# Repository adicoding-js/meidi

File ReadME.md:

# MIDI Keypad

()

A custom USB MIDI controller built from scratch following Kai's MIDI Keypad tutorial. No stock firmware, no base project to extend, the tutorial hands you a KiCad library and component options and says figure out your own layout, so this is my own hardware config and (once I get to it) my own firmware mapping it to MIDI.

## What it is

7 capacitive touch keys mapped to a scale off a root note, plus a rotary encoder for octave shifting, two slide potentiometers and a rotary potentiometer for CC control (mod wheel, volume, filter cutoff), and 3 push buttons rounding out the control surface. Everything runs off a Waveshare ESP32-S3-Zero, through-hole and SMD components on a single PCB.

### Layout

| Control | Function |
|---|---|
| TOUCH1–7 | 7 notes, chromatic from a root note (capacitive touch, exposed copper pads) |
| Rotary encoder | Octave shift up/down |
| Encoder push | Reset to default octave |
| Slider 1 | Mod wheel (CC1) |
| Slider 2 | Volume (CC7) |
| Rotary pot | Filter cutoff / expression (CC11) |
| SW1–3 | Extra notes / mode switches (TBD) |

## Why?

Unlike a guide that hands you a finished sketch and hardware spec, this tutorial is intentionally open ended, pick your own components, your own layout, your own firmware. So there's no "stock" version to diverge from here, the departure from the guide is the whole point of following it. What's here is my own schematic built off the tutorial's component options (capacitive touch keys, EC11 encoder, slide pots), with my own control mapping on top.

## Status

Schematic and PCB layout are done in KiCad, board hasn't been fabbed or ordered yet. Firmware hasn't been written. This readme documents the plan, not a finished build, updating as I actually get hardware in hand and start writing code.

## Bill of materials (BOM)

| Item | Description | Qty | Unit Price (USD) | Line Total (USD) | Link |
|------|-------------|-----|------------------|------------------|------|
| 1 | Waveshare ESP32-S3-Zero, main microcontroller | 1 | $6.06 | $6.06 | [Robocraze](https://robocraze.com/products/waveshare-esp32-s3-zero-development-board-240mhz) |
| 2 | EC11 15 mm rotary encoder module with push switch | 1 | $0.70 | $0.70 | [Robocraze](https://robocraze.com/collections/sensors?page=21) |
| 3 | Kailh Choc low-profile push-button switches | i coduln'd find these but i have these |
| 4 | Bourns 10k slide potentiometer, 45 mm travel, 15 mm shaft, pack of 2 | 1 pack | $18.10 | $18.10 | [Amazon India](https://www.amazon.in/BOURNS-Potentiometer-Travel-Single-Linear/dp/B079ZP3LS5) |
| 5 | 10k rotary potentiometer with knob | 1 | $0.36 | $0.36 | [Robocraze](https://robocraze.com/products/10k-pot-potentiometer-with-knob) |
| 6 | Capacitive touch pads — exposed copper on PCB | 7 | $0.00 | $0.00 | PCB feature, no separate part |
| 7 | 1×40 2.54 mm female header strip, for ESP32-S3-Zero mounting | 1 | $0.13 | $0.13 | [Robocraze](https://robocraze.com/products/40x1-female-berg-strip) |
| 8 | Optional: 6×6×8 mm tactile buttons, 10-pack, if not using Choc switches | 1 pack | $0.21 | $0.21 | [Robocraze](https://robocraze.com/collections/push-buttons) |
| 9 | JLCPCB 2-layer PCB, up to 100×100 mm, 5 pcs | 1 order | From $2.00 | From $2.00 + shipping | [JLCPCB](https://jlcpcb.com/ads/pcb-prototype) |
| | **Known-parts subtotal** | | | **$25.34** | |
| | **Grand total** | | | **$27.34 + PCB shipping + unresolved Choc switches** | |

## Software

Planning to use TinyUSB or Arduino MIDI library for USB MIDI over the ESP32-S3. Nothing written yet, will add once the board's in hand.

## Known issues

Nothing as far as i know

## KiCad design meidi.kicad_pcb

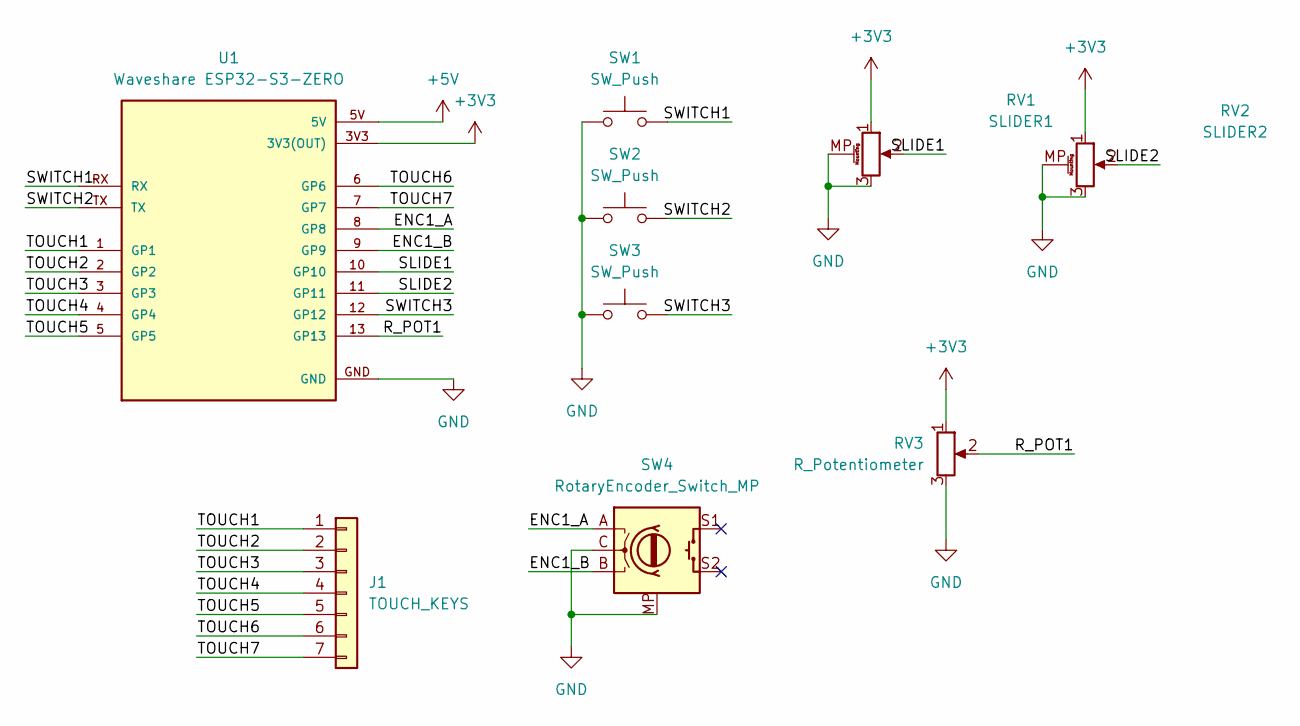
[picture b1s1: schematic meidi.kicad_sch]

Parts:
J1: TOUCH_KEYS; capacitive
RV1: SLIDER1; Potentiometer_Bourns_PTA1543_Single_Slide
RV2: SLIDER2; Potentiometer_Bourns_PTA1543_Single_Slide
RV3: R_Potentiometer; Potentiometer_Alps_RK163_Single_Horizontal
SW1, SW2, SW3: SW_Push; Kailh Choc Low-Profile Switches
SW4: RotaryEncoder_Switch_MP; RotaryEncoder_Alps_EC11E-Switch_Vertical_H20mm
U1: Waveshare ESP32-S3-ZERO; Waveshare ESP32-S3-Zero; PARTREV NA

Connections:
+3V3: RV1.1, RV2.1, RV3.1, U1.3V3 (3V3(OUT))
+5V: U1.5V
/ENC1_A: SW4.A, U1.8 (GP8)
/ENC1_B: SW4.B, U1.9 (GP9)
/R_POT1: RV3.2, U1.13 (GP13)
/SLIDE1: RV1.2, U1.10 (GP10)
/SLIDE2: RV2.2, U1.11 (GP11)
/SWITCH1: SW1.2, U1.RX
/SWITCH2: SW2.2, U1.TX
/SWITCH3: SW3.2, U1.12 (GP12)
/TOUCH1: J1.1, U1.1 (GP1)
/TOUCH2: J1.2, U1.2 (GP2)
/TOUCH3: J1.3, U1.3 (GP3)
/TOUCH4: J1.4, U1.4 (GP4)
/TOUCH5: J1.5, U1.5 (GP5)
/TOUCH6: J1.6, U1.6 (GP6)
/TOUCH7: J1.7, U1.7 (GP7)
GND: RV1.3, RV1.MP (MountPin), RV2.3, RV2.MP (MountPin), RV3.3, SW1.1, SW2.1, SW3.1, SW4.C, SW4.MP, U1.GND

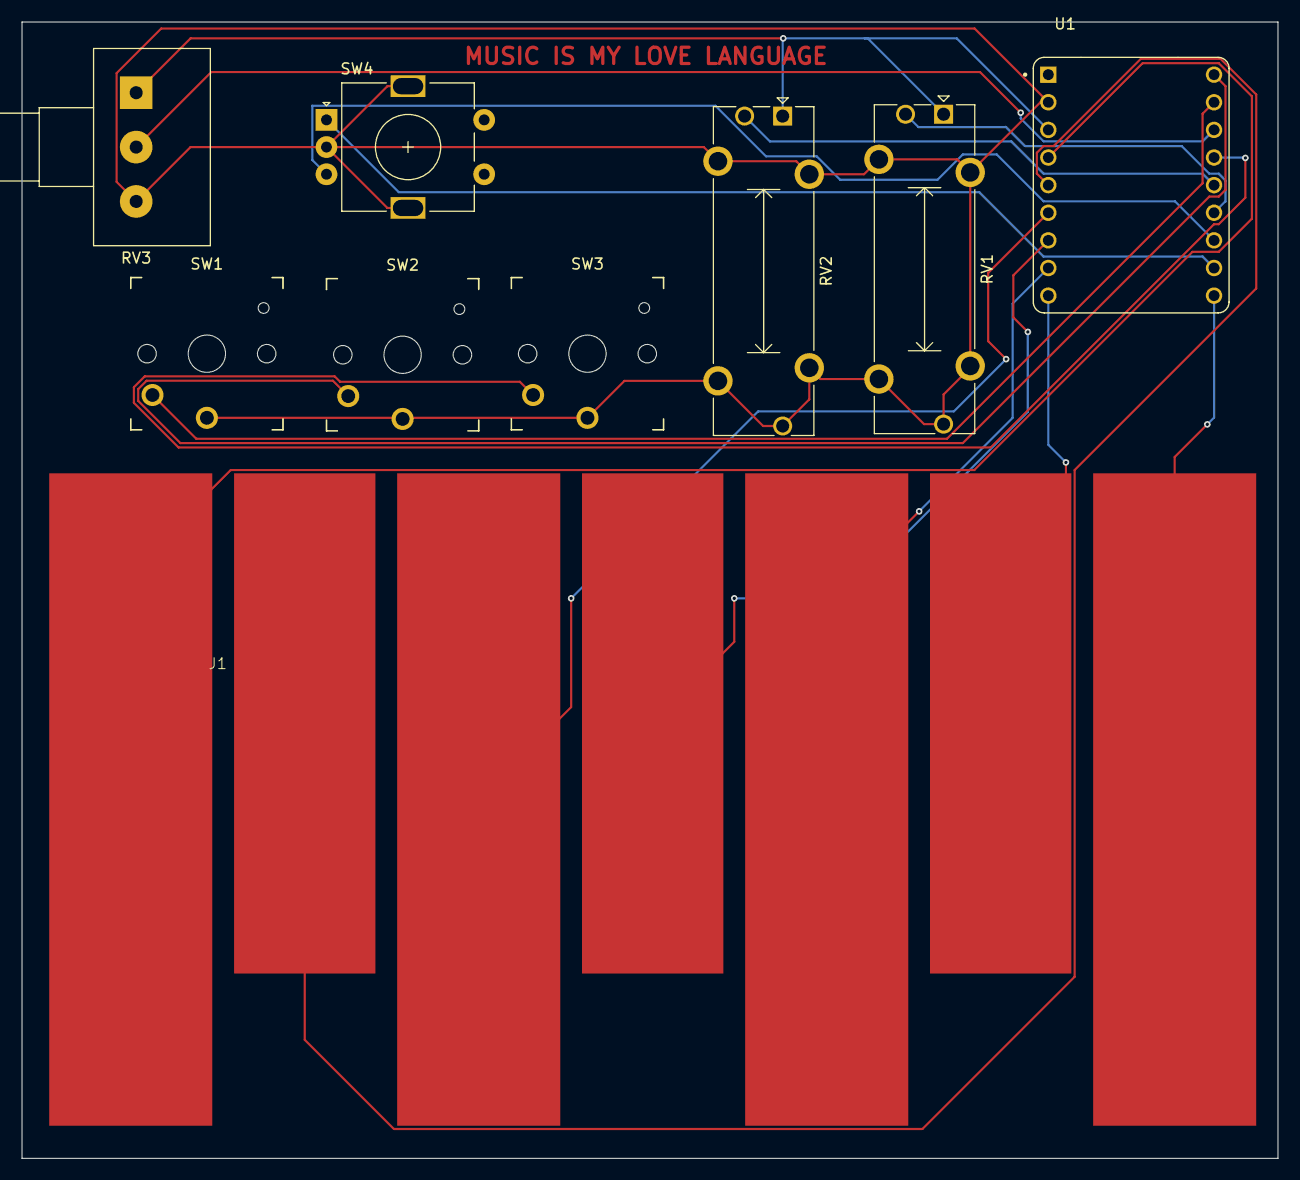
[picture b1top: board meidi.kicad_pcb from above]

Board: 2 copper layers, 115.5 x 104.5 mm, 9 parts (0 on the bottom side), 17 nets.
